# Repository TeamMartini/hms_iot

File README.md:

# IoT
빌리지의 정보를 수집하기 위한 IoT 기기 소프트웨어

## Env
| 환경  | 버전 |
|  -----  | --- |
| Node  | 15.5.0 |
| Node-RED | 1.3.3 |
| Arduino | 1.8.15 |
| ESP32 board Manager | 1.0.2 |
| Mosquitto | 2.0.10 |

## Install

레포지토리 설치
```shell
npm install -g node-red
```

실행
```
node-red
```

디바이스 설정 변경 시 esp32_mqtt_client_test.ino에서 ssid, password, mqtt_server, mqtt_user, mqtt_password 각자 환경에 맞게 변경

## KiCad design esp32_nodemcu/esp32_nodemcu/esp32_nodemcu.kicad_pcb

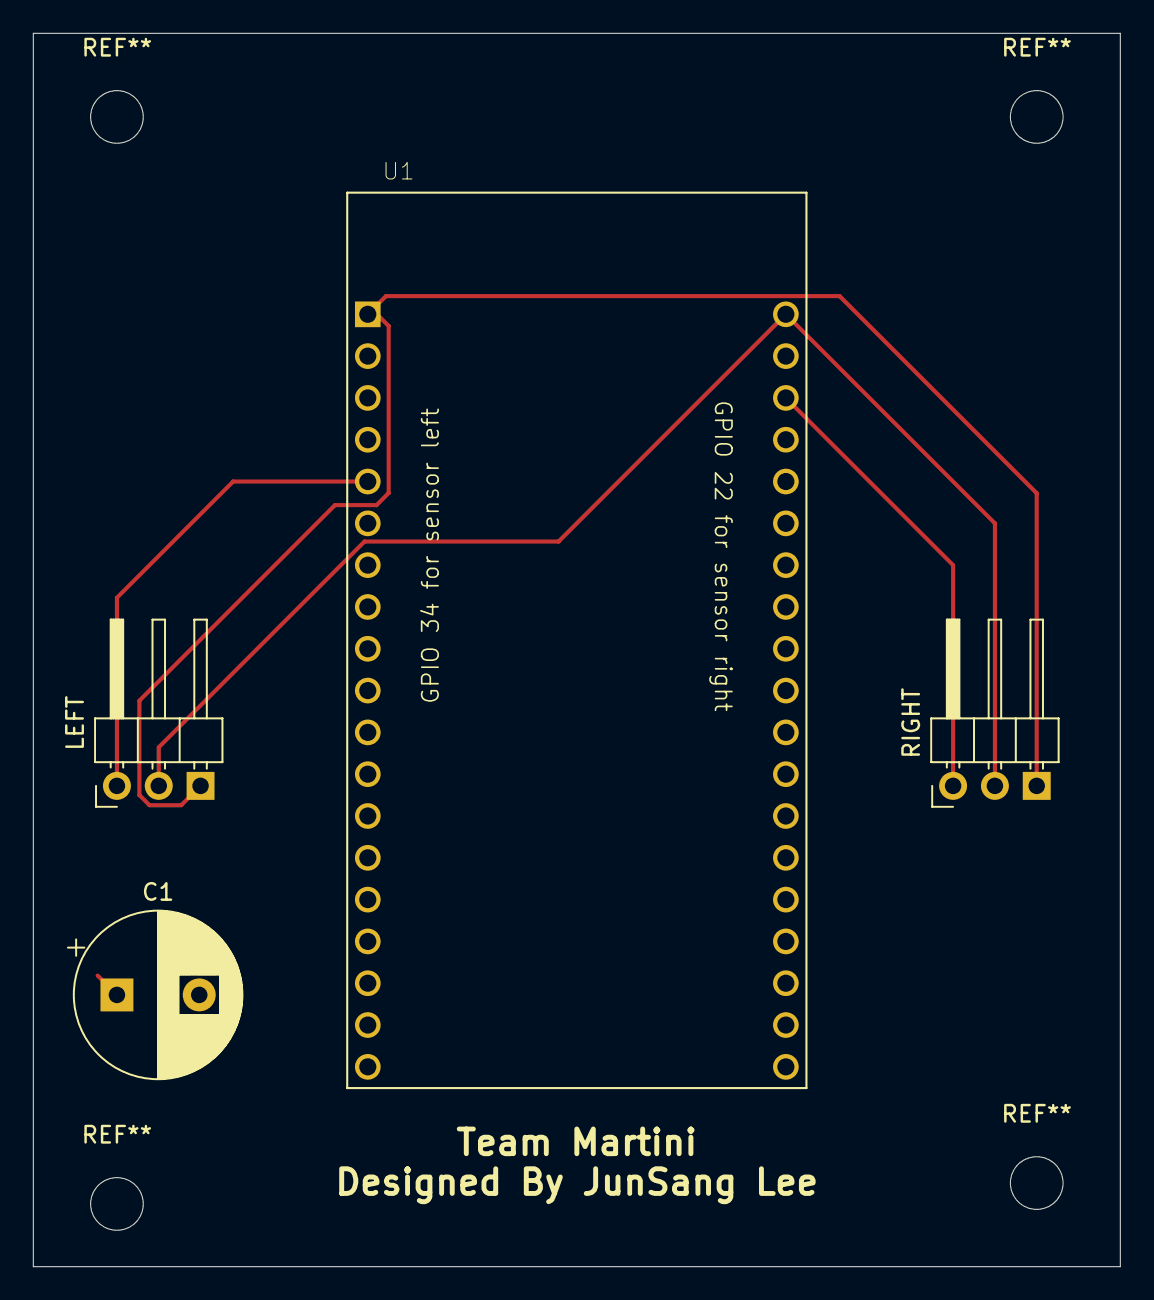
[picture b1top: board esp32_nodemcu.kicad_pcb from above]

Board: 2 copper layers, 66.0 x 74.9 mm, 4 parts (0 on the bottom side), 6 nets.

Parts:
C1: CAP; CP_Radial_D10.0mm_P5.00mm
LEFT: szh-ssbh-002
RIGHT: szh-ssbh-002
U1: ESP32-DEVKITC-32D; MODULE_ESP32-DEVKITC-32D

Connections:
unnamed: C1.1, U1.2
unnamed: C1.2, U1.14
unnamed: LEFT.1, RIGHT.1, U1.1
unnamed: LEFT.2, RIGHT.2, U1.20
unnamed: LEFT.3, U1.5
unnamed: RIGHT.3, U1.22

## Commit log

2021-03-20 initial settings
2021-04-05 app.js => node.js로 mongodb 데이터베이스 , 테이블, 생성 뒤 값 집어넣기 테스트 flows.json => node-red를 이용해 esp32에서 mqtt로 mac주소값 받아 브라우저로 표시 및 mongodb에 저장 png파일 => 몽고디비 저장 결과
2021-04-19 아두이노 양방향 출입 카운터 + mqtt 통신
2021-04-27 kicad를 이용한 pcb 도면 제작중
2021-05-07 pcb update
2021-05-26 update pcb
2021-05-26 esp_cam update
2021-05-26 test
